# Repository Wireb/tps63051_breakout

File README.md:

# TPS63051 breakout
This design is a simple breakout card for the TPS63051 buck boost 2.5V to 5.5V Vin to 3.3V @ 0.5A Vout regulator. 
Main reason was to run the reg though it's paces and see how bad the package was to hand place and solder. (not too bad better than solder lug packages) 
So far no issues found tested at 2.5V to 5.5V in and no load, 220mA and 440mA Vout (all stable at 3.3Vout) 
License is MIT so do what you want with it just don't litigate me. 

## KiCad
This is a KiCad 5.0 project. 

## documentation
This is a XLS/PDF dump of the spreadsheet documentation I was using during development. 

## OSHpark PCBs
PCB design can be found here:
https://www.oshpark.com/shared_projects/cPTJPkIs

Copyright (c) 2018 Peter Shabino

Permission is hereby granted, free of charge, to any person obtaining a copy of this hardware, software, and associated documentation files 
(the "Product"), to deal in the Product without restriction, including without limitation the rights to use, copy, modify, merge, publish, 
distribute, sublicense, and/or sell copies of the Product, and to permit persons to whom the Product is furnished to do so, subject to the 
following conditions:

The above copyright notice and this permission notice shall be included in all copies or substantial portions of the Product.

THE PRODUCT IS PROVIDED "AS IS", WITHOUT WARRANTY OF ANY KIND, EXPRESS OR IMPLIED, INCLUDING BUT NOT LIMITED TO THE WARRANTIES OF 
MERCHANTABILITY, FITNESS FOR A PARTICULAR PURPOSE AND NONINFRINGEMENT. IN NO EVENT SHALL THE AUTHORS OR COPYRIGHT HOLDERS BE LIABLE 
FOR ANY CLAIM, DAMAGES OR OTHER LIABILITY, WHETHER IN AN ACTION OF CONTRACT, TORT OR OTHERWISE, ARISING FROM, OUT OF OR IN CONNECTION 
WITH THE PRODUCT OR THE USE OR OTHER DEALINGS IN THE PRODUCT.

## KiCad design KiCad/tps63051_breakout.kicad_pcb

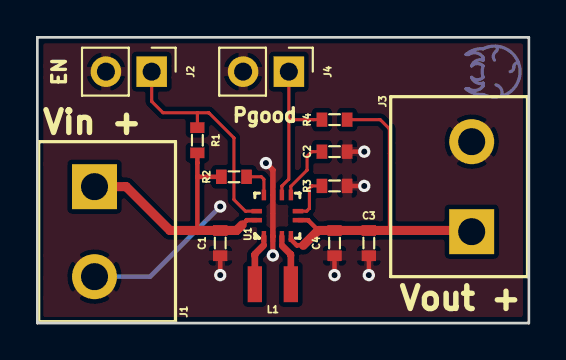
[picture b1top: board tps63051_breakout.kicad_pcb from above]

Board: 2 copper layers, 27.3 x 15.9 mm, 15 parts (1 on the bottom side), 10 nets.

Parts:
C1, C3, C4: 10uF; 0603
C2: 1nF; 0603
J1: Vin; DG301-5.002P-12
J2: EN; Pin_Header_Straight_1x02_Pitch2.54mm
J3: Vout; DG301-5.002P-12
J4: Pgood; Pin_Header_Straight_1x02_Pitch2.54mm
L1: 1.5uH; SMT_passive_1008
R1: 100k; 0603
R2, R3: 0; 0603
R4: 1M; 0603
U1: TPS63051; TI_VQFN_12
icon1: Metroid; metroid

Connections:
GND: C1.2, C2.2, C3.2, C4.2, J1.2, J2.2, J3.2, J4.2, R3.2, U1.2, U1.9
unnamed: C1.1, J1.1, R1.1, R2.2, U1.12
unnamed: C2.1, U1.7
unnamed: C3.1, C4.1, J3.1, R4.1, U1.4, U1.5
unnamed: J2.1, R1.2, U1.11
unnamed: J4.1, R4.2, U1.8
unnamed: L1.1, U1.3
unnamed: L1.2, U1.1
unnamed: R2.1, U1.10
unnamed: R3.1, U1.6

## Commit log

2018-09-02 :circus_tent: Added .gitattributes & .gitignore files
2018-09-02 First post

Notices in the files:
KiCad/tps63051_breakout.kicad_pcb:
MIT License
